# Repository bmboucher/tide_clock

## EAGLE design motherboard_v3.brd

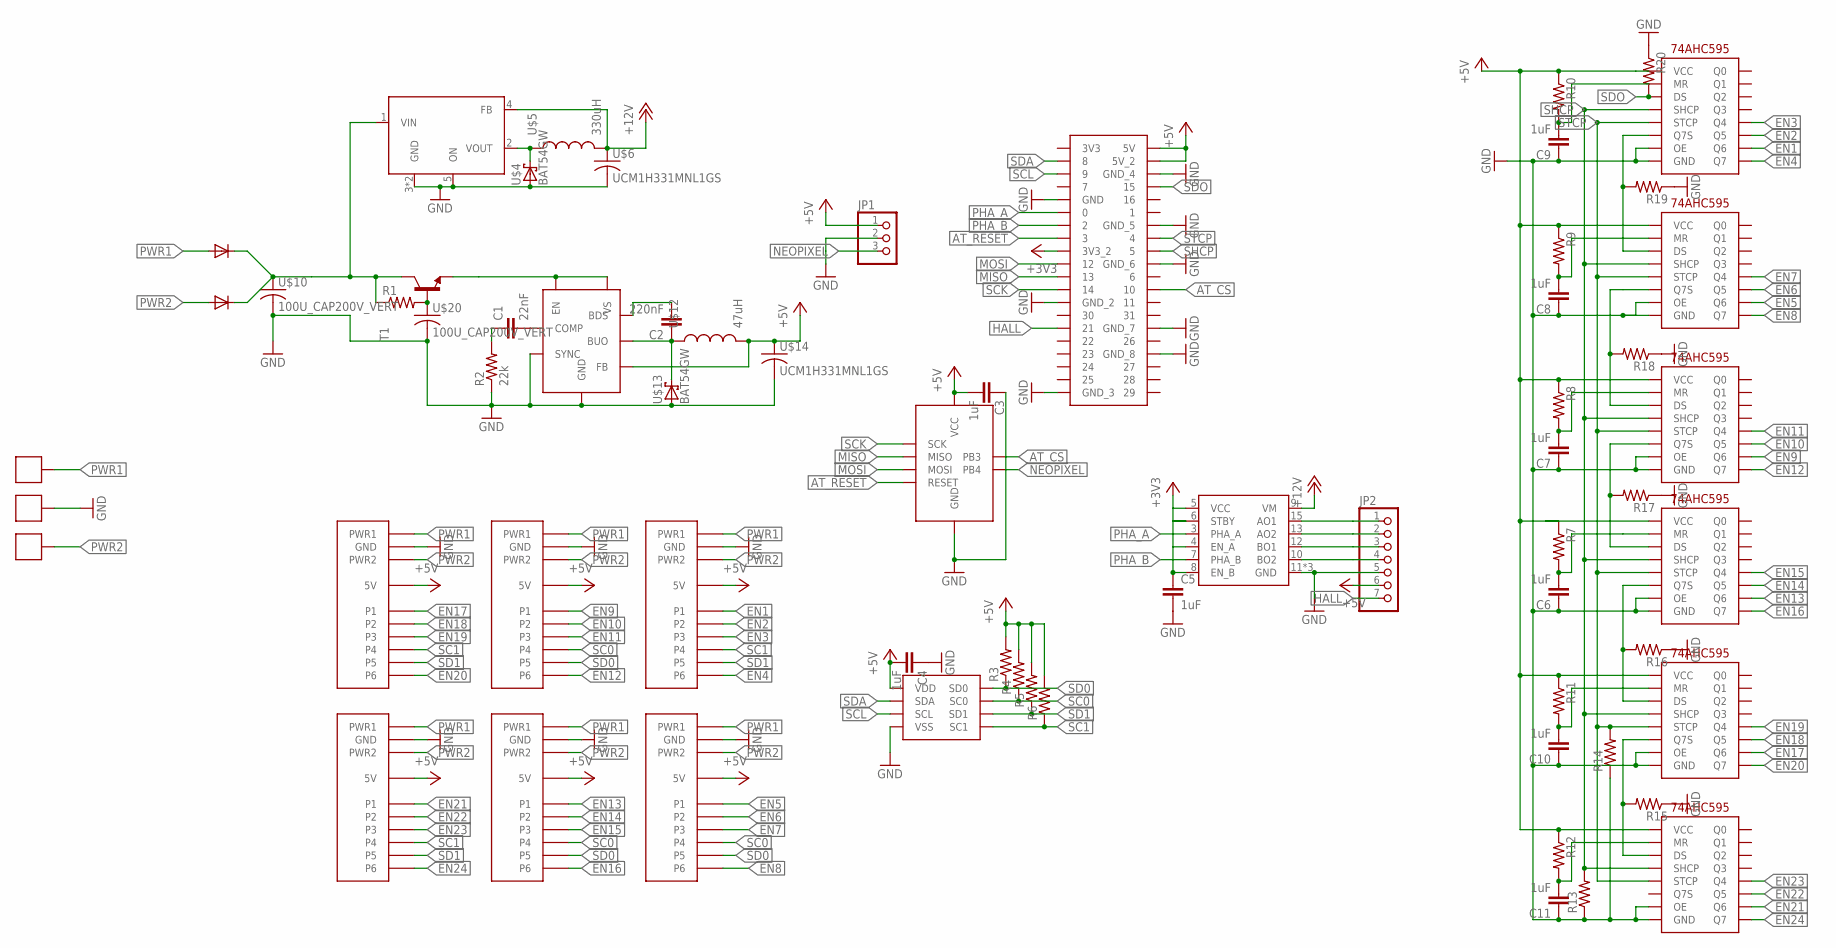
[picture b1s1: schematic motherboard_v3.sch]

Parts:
B1, B2, B3, B4, B5, B6: PCIE_SOCKET
C1: 22nF; C0805
C2: 220nF; C0805
C3, C4, C5, C6, C7, C8, C9, C10, C11: 1uF; C0805
JP1: PINHD-1X3; 1X03
JP2: PINHD-1X7; 1X07
R1: R-US_R1206; R1206
R2: 22k; R1206
R3, R4, R5, R6, R7, R8, R9, R10, R11, R12, R13, R14, R15, R16, R17, R18, R19, R20: R-US_R0805; R0805
T1: -NPN-SOT23-EBC; SOT23-EBC
U1: IFX91041EJV50XUMA1; SOIC127P600X170-8
U$1: RPI_SOCKET; 40PIN_SOCKET
U$2: TC78H620FNG; SSOP16
U$3: TL2575HV-12IKTTR; TO170P1524X483-6
U$4, U$13: BAT54GW; SOD3616X130
U$5: 330uH; SRN8040TA
U$6, U$14: UCM1H331MNL1GS; CAPAE1030X1050
U$7, U$22, U$23, U$24, U$25, U$26: 74HC595_QFN; QFN50P250X350X100-16
U$8, U$9: BAS16GW; SOD3616X130
U$10, U$20: 100U_CAP200V_VERT; VERT_CAP
U$11: ATTINY85; SOIC127P599X175-8
U$12: 47uH; SRN8040TA
U$17, U$18, U$19: 1935310
U$21: PCA9540BDP; TSSOP8

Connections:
+3V3: C5.1, U$1.P17 (3V3_2), U$2.4 (EN_A), U$2.5 (VCC), U$2.6 (STBY), U$2.8 (EN_B)
+5V: B1.5V_1 (5V), B1.5V_2 (5V), B2.5V_1 (5V), B2.5V_2 (5V), B3.5V_1 (5V), B3.5V_2 (5V), B4.5V_1 (5V), B4.5V_2 (5V), B5.5V_1 (5V), B5.5V_2 (5V), B6.5V_1 (5V), B6.5V_2 (5V), C3.2, C4.2, JP1.1, JP2.6, R3.2, R4.2, R5.2, R6.2, R7.1, R8.1, R9.1, R10.1, R11.1, R12.1, U1.4 (FB), U$1.P2 (5V), U$1.P4 (5V_2), U$7.P16 (VCC), U$11.8 (VCC), U$12.P$2 (2), U$14.1, U$21.3 (VDD), U$22.P16 (VCC), U$23.P16 (VCC), U$24.P16 (VCC), U$25.P16 (VCC), U$26.P16 (VCC)
+12V: U$2.9 (VM), U$3.4 (FB), U$5.P$2 (2), U$6.1
AT_CS: U$1.P24 (10), U$11.2 (PB3)
AT_RESET: U$1.P15 (3), U$11.1 (RESET)
EN1: B1.P1, U$7.P6 (Q6)
EN2: B1.P2, U$7.P5 (Q5)
EN3: B1.P3, U$7.P4 (Q4)
EN4: B1.P6, U$7.P7 (Q7)
EN5: B2.P1, U$22.P6 (Q6)
EN6: B2.P2, U$22.P5 (Q5)
EN7: B2.P3, U$22.P4 (Q4)
EN8: B2.P6, U$22.P7 (Q7)
EN9: B3.P1, U$23.P6 (Q6)
EN10: B3.P2, U$23.P5 (Q5)
EN11: B3.P3, U$23.P4 (Q4)
EN12: B3.P6, U$23.P7 (Q7)
EN13: B4.P1, U$24.P6 (Q6)
EN14: B4.P2, U$24.P5 (Q5)
EN15: B4.P3, U$24.P4 (Q4)
EN16: B4.P6, U$24.P7 (Q7)
EN17: B5.P1, U$25.P6 (Q6)
EN18: B5.P2, U$25.P5 (Q5)
EN19: B5.P3, U$25.P4 (Q4)
EN20: B5.P6, U$25.P7 (Q7)
EN21: B6.P1, U$26.P6 (Q6)
EN22: B6.P2, U$26.P5 (Q5)
EN23: B6.P3, U$26.P4 (Q4)
EN24: B6.P6, U$26.P7 (Q7)
GND: B1.GND1 (GND), B1.GND2 (GND), B2.GND1 (GND), B2.GND2 (GND), B3.GND1 (GND), B3.GND2 (GND), B4.GND1 (GND), B4.GND2 (GND), B5.GND1 (GND), B5.GND2 (GND), B6.GND1 (GND), B6.GND2 (GND), C3.1, C4.1, C5.2, C6.1, C7.1, C8.1, C9.1, C10.1, C11.1, JP1.2, JP2.5, R2.1, R13.1, R14.1, R15.1, R16.1, R17.1, R18.1, R19.1, R20.1, U1.1 (SYNC), U1.2 (GND), U1.PAD (GND), U$1.P6 (GND_4), U$1.P9 (GND), U$1.P14 (GND_5), U$1.P20 (GND_6), U$1.P25 (GND_2), U$1.P30 (GND_7), U$1.P34 (GND_8), U$1.P39 (GND_3), U$2.11 (GND), U$2.14 (GND), U$2.16 (GND), U$3.3 (GND), U$3.5 (ON), U$3.6 (GND), U$4.2 (A), U$6.2, U$7.P8 (GND), U$7.P13 (OE), U$7.P$1 (GND), U$10.P$4 (2), U$11.4 (GND), U$13.2 (A), U$14.2, U$18.P$1, U$18.P$2, U$20.P$4 (2), U$21.6 (VSS), U$22.P8 (GND), U$22.P13 (OE), U$22.P$1 (GND), U$23.P8 (GND), U$23.P13 (OE), U$23.P$1 (GND), U$24.P8 (GND), U$24.P13 (OE), U$24.P$1 (GND), U$25.P8 (GND), U$25.P13 (OE), U$25.P$1 (GND), U$26.P8 (GND), U$26.P13 (OE), U$26.P$1 (GND)
HALL: JP2.7, U$1.P29 (21)
MISO: U$1.P21 (13), U$11.6 (MISO)
MOSI: U$1.P19 (12), U$11.5 (MOSI)
unnamed: T1.E, U1.7 (EN), U1.8 (VS)
unnamed: R1.2, T1.B, U$20.P$3 (1)
unnamed: R1.1, T1.C, U$3.1 (VIN), U$8.1 (C), U$9.1 (C), U$10.P$3 (1)
unnamed: C1.2, U1.3 (COMP)
unnamed: C1.1, R2.2
unnamed: C2.2, U1.5 (BDS)
unnamed: C2.1, U1.6 (BUO), U$12.P$1 (1), U$13.1 (C)
unnamed: R19.2, U$7.P9 (Q7S), U$22.P14 (DS)
unnamed: JP2.1, U$2.15 (AO1)
unnamed: JP2.2, U$2.13 (AO2)
unnamed: JP2.3, U$2.12 (BO1)
unnamed: JP2.4, U$2.10 (BO2)
unnamed: U$3.2 (VOUT), U$4.1 (C), U$5.P$1 (1)
unnamed: C6.2, R7.2, U$24.P10 (MR)
unnamed: R18.2, U$22.P9 (Q7S), U$23.P14 (DS)
unnamed: R17.2, U$23.P9 (Q7S), U$24.P14 (DS)
unnamed: C7.2, R8.2, U$23.P10 (MR)
unnamed: C8.2, R9.2, U$22.P10 (MR)
unnamed: C9.2, R10.2, U$7.P10 (MR)
unnamed: R16.2, U$24.P9 (Q7S), U$25.P14 (DS)
unnamed: C10.2, R11.2, U$25.P10 (MR)
unnamed: C11.2, R12.2, U$26.P10 (MR)
unnamed: R15.2, U$25.P9 (Q7S), U$26.P14 (DS)
NEOPIXEL: JP1.3, U$11.3 (PB4)
PHA_A: U$1.P11 (0), U$2.3 (PHA_A)
PHA_B: U$1.P13 (2), U$2.7 (PHA_B)
PWR1: B1.PWR1_1 (PWR1), B1.PWR1_2 (PWR1), B2.PWR1_1 (PWR1), B2.PWR1_2 (PWR1), B3.PWR1_1 (PWR1), B3.PWR1_2 (PWR1), B4.PWR1_1 (PWR1), B4.PWR1_2 (PWR1), B5.PWR1_1 (PWR1), B5.PWR1_2 (PWR1), B6.PWR1_1 (PWR1), B6.PWR1_2 (PWR1), U$8.2 (A), U$17.P$1, U$17.P$2
PWR2: B1.PWR2_1 (PWR2), B1.PWR2_2 (PWR2), B2.PWR2_1 (PWR2), B2.PWR2_2 (PWR2), B3.PWR2_1 (PWR2), B3.PWR2_2 (PWR2), B4.PWR2_1 (PWR2), B4.PWR2_2 (PWR2), B5.PWR2_1 (PWR2), B5.PWR2_2 (PWR2), B6.PWR2_1 (PWR2), B6.PWR2_2 (PWR2), U$9.2 (A), U$19.P$1, U$19.P$2
SC0: B2.P4, B3.P4, B4.P4, R4.1, U$21.5 (SC0)
SC1: B1.P4, B5.P4, B6.P4, R6.1, U$21.8 (SC1)
SCK: U$1.P23 (14), U$11.7 (SCK)
SCL: U$1.P5 (9), U$21.1 (SCL)
SD0: B2.P5, B3.P5, B4.P5, R3.1, U$21.4 (SD0)
SD1: B1.P5, B5.P5, B6.P5, R5.1, U$21.7 (SD1)
SDA: U$1.P3 (8), U$21.2 (SDA)
SDO: R20.2, U$1.P8 (15), U$7.P14 (DS)
SHCP: R13.2, U$1.P18 (5), U$7.P11 (SHCP), U$22.P11 (SHCP), U$23.P11 (SHCP), U$24.P11 (SHCP), U$25.P11 (SHCP), U$26.P11 (SHCP)
STCP: R14.2, U$1.P16 (4), U$7.P12 (STCP), U$22.P12 (STCP), U$23.P12 (STCP), U$24.P12 (STCP), U$25.P12 (STCP), U$26.P12 (STCP)

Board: 2 copper layers, 65 parts (27 on the bottom side), 71 nets, no tracks yet.

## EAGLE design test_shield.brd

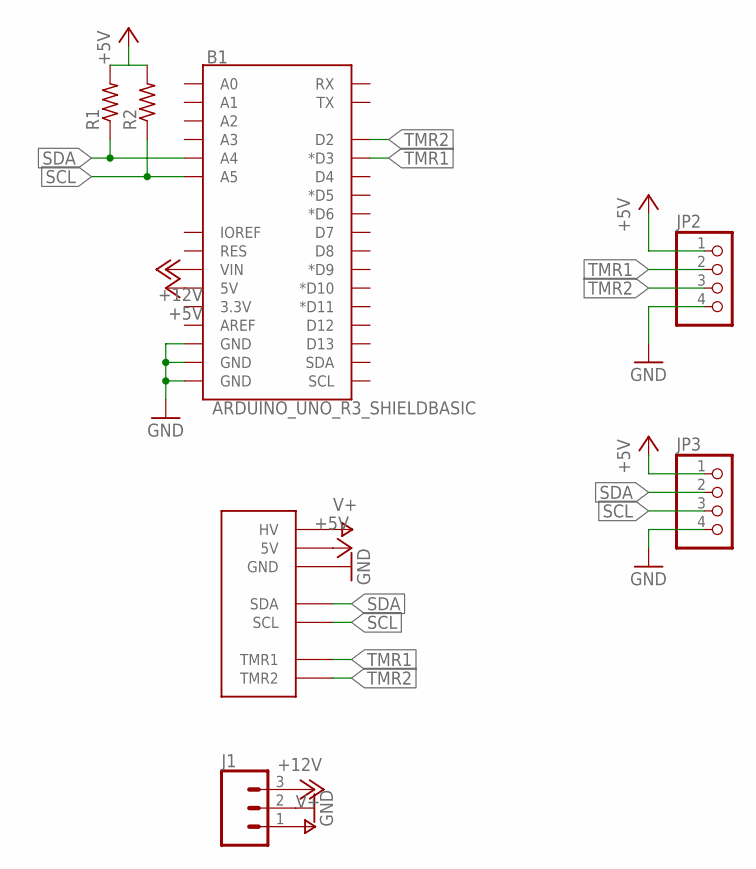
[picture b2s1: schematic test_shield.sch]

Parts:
B1: ARDUINO_UNO_R3_SHIELDBASIC; UNO_R3_SHIELD
J1: CONN_03-SCREW-5MM; SCREWTERMINAL-5MM-3
JP1: PCIE_RA
JP2, JP3: PINHD-1X4; 1X04
R1, R2: R-US_0207/10; 0207/10

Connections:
+5V: B1.5V, JP1.A12 (5V), JP1.A13 (5V), JP1.A14 (5V), JP1.B12 (5V), JP1.B13 (5V), JP1.B14 (5V), JP2.1, JP3.1, R1.2, R2.2
+12V: B1.VIN, J1.3
GND: B1.GND@0 (GND), B1.GND@1 (GND), B1.GND@2 (GND), J1.2, JP1.A1 (GND), JP1.A2 (GND), JP1.A3 (GND), JP1.B1 (GND), JP1.B2 (GND), JP1.B3 (GND), JP2.4, JP3.4
SCL: B1.A5, JP1.A5 (SCL), JP1.B5 (SCL), JP3.3, R2.1
SDA: B1.A4, JP1.A6 (SDA), JP1.B6 (SDA), JP3.2, R1.1
TMR1: B1.D3 (*D3), JP1.A8 (TMR1), JP1.B8 (TMR1), JP2.2
TMR2: B1.D2, JP1.A9 (TMR2), JP1.B9 (TMR2), JP2.3
V+: J1.1, JP1.A16 (HV), JP1.A17 (HV), JP1.A18 (HV), JP1.B16 (HV), JP1.B17 (HV), JP1.B18 (HV)

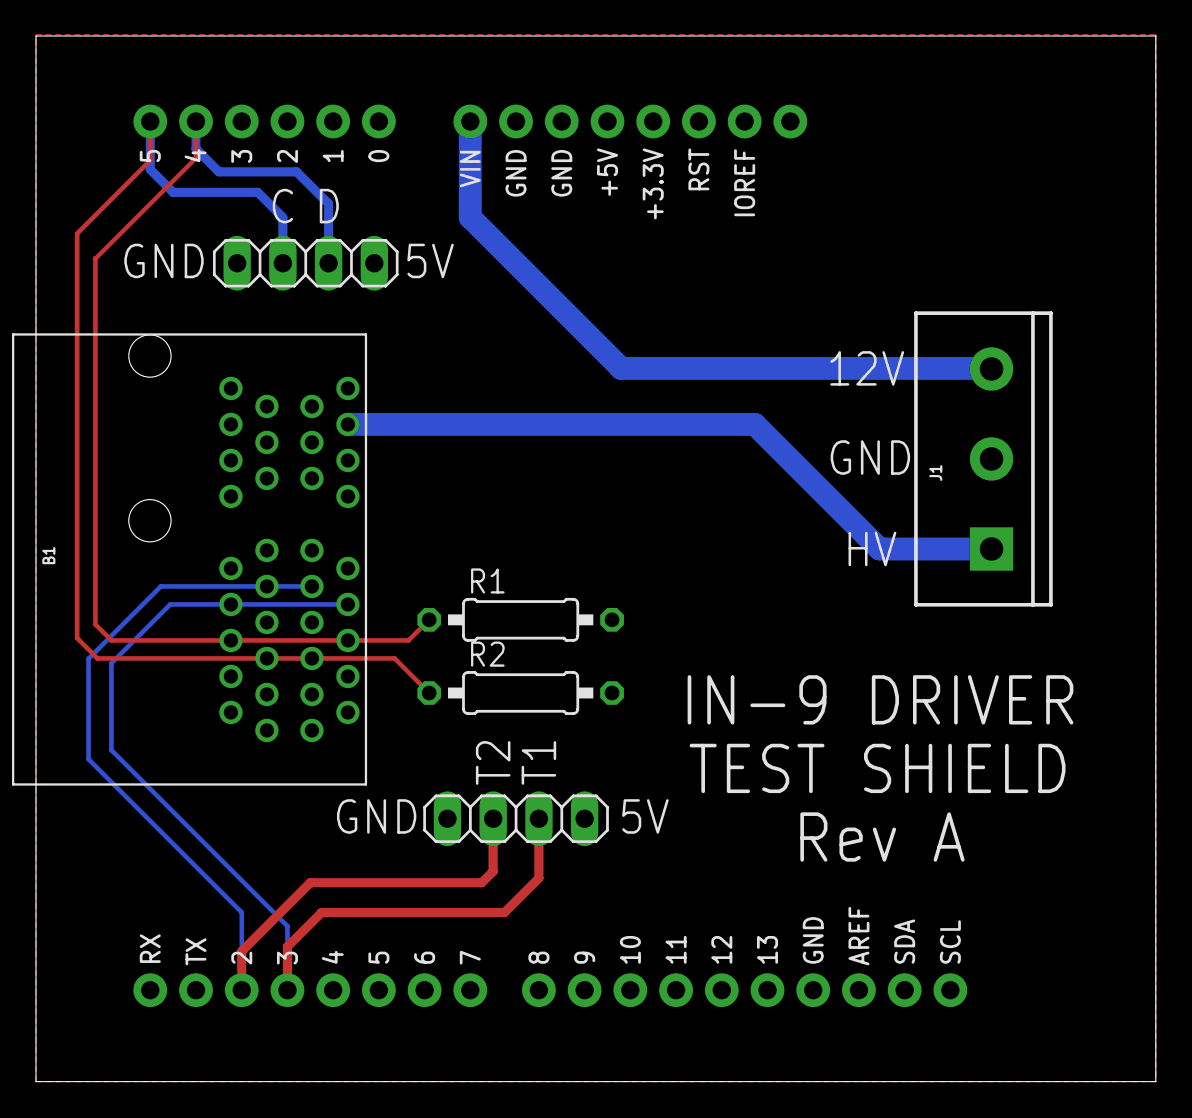
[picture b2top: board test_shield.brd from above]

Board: 2 copper layers, 62.2 x 58.1 mm, 7 parts (0 on the bottom side), 8 nets.

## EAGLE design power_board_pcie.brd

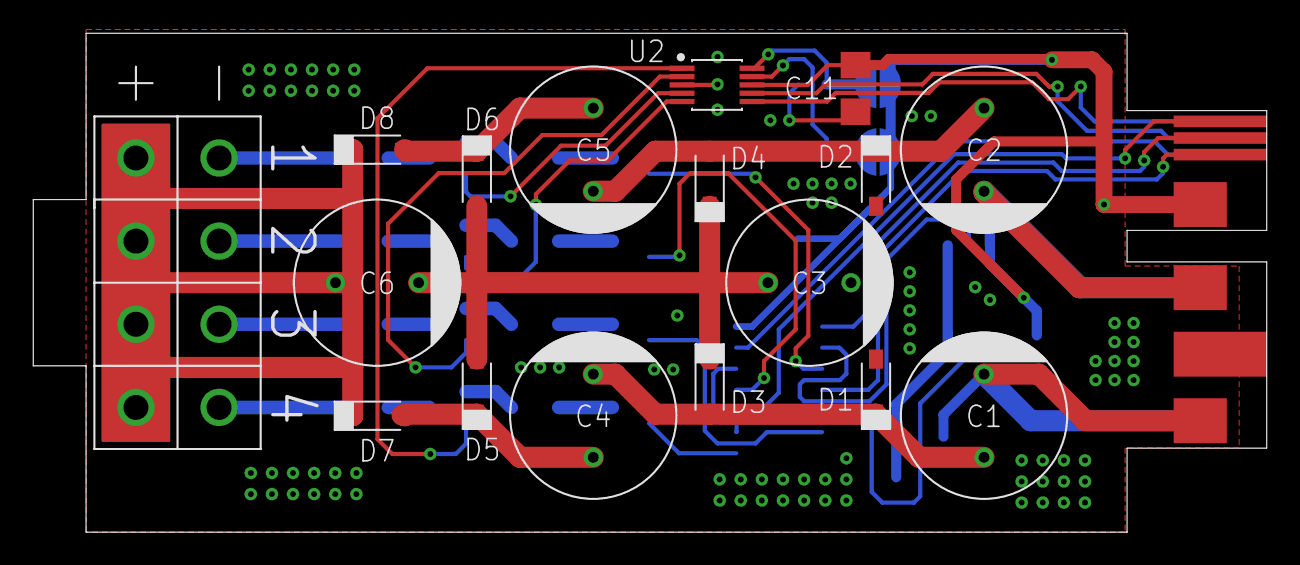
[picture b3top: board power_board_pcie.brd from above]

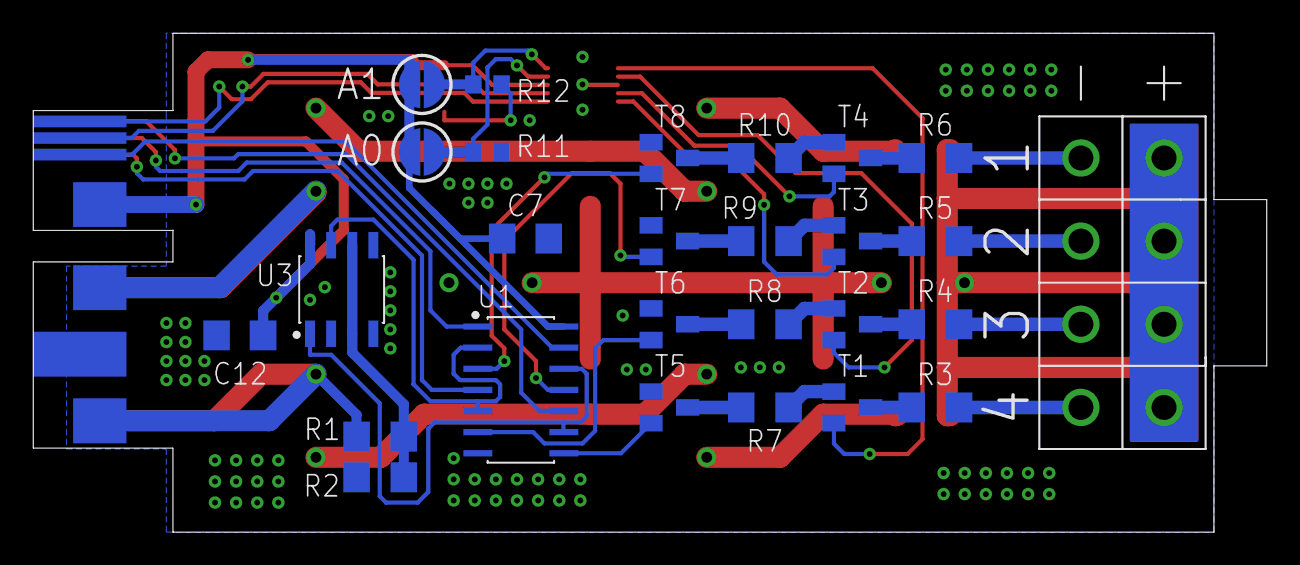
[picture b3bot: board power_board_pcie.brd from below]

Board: 2 copper layers, 74.2 x 30.0 mm, 44 parts (26 on the bottom side), 45 nets.

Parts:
C1, C2, C3, C4, C5, C6: 100U_CAP
C7, C11, C12: C1206
D1, D2, D3, D4, D5, D6, D7, D8: BAS16GW; SOD3616X130
J1: PCIE_EDGE
JP1, JP2: JUMPER-SMT_2_NO_SILK_ROUND; SMT-JUMPER_2_NO_SILK_ROUND
R1, R2, R3, R4, R5, R6, R7, R8, R9, R10: R1206
R11, R12: R0603
T1, T2, T3, T4, T5, T6, T7, T8: SOT23-EBC
U1: 74HCT08D; SOIC127P600X175-14
U2: DAC5574; SOP50P490X110-10
U3: AZ4558CMTR-G1; SOIC127P600X175-8
U$3: POWER_EDGE

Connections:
+5V: C7.1, C11.1, C12.1, J1.PWR3, J1.PWR3_2, JP1.1, JP2.1, U1.14, U2.8, U3.8
EN1: J1.P6, U1.13
EN2: J1.P3, U1.10
EN3: J1.P2, U1.1
EN4: J1.P1, U1.4
GND: C3.C, C7.2, C11.2, C12.2, D1.2, D2.2, J1.P$2, J1.P$5, R2.1, R11.2, R12.2, T5.E, T6.E, T7.E, T8.E, U1.7, U2.3, U3.2, U3.4, U3.5
unnamed: R7.2, T1.E
unnamed: R1.1, R2.2, U3.3, U3.6
unnamed: R3.1, T1.C
unnamed: C3.A, C6.C, D3.1, D4.1, D5.2, D6.2
unnamed: C1.A, C4.C, D1.1, D3.2
unnamed: C2.A, C5.C, D2.1, D4.2
unnamed: C4.A, D5.1, D7.2
unnamed: C5.A, D6.1, D8.2
unnamed: R3.2, U$3.C1
unnamed: R4.2, U$3.C2
unnamed: R5.2, U$3.C3
unnamed: R4.1, T2.C
unnamed: R6.2, U$3.C4
unnamed: R5.1, T3.C
unnamed: R6.1, T4.C
unnamed: R7.1, T5.C
unnamed: T2.B, U2.2
unnamed: T3.B, U2.5
unnamed: T4.B, U2.4
unnamed: T1.B, U2.1
unnamed: R8.2, T2.E
unnamed: R9.2, T3.E
unnamed: R10.2, T4.E
unnamed: R8.1, T6.C
unnamed: R9.1, T7.C
unnamed: R10.1, T8.C
unnamed: JP1.2, R11.1, U2.9
unnamed: JP2.2, R12.1, U2.10
PH_EN1: U1.9, U1.12, U3.1
PH_EN2: U1.2, U1.5, U3.7
PWR1: C1.C, J1.P$1, J1.P$4, R1.2
PWR2: C2.C, J1.P$3, J1.P$6
SCL: J1.P4, U2.6
SDA: J1.P5, U2.7
SW1: T8.B, U1.3
SW2: T6.B, U1.6
SW3: T5.B, U1.8
SW4: T7.B, U1.11
V+: C6.A, D7.1, D8.1, U$3.A1, U$3.A2, U$3.A3, U$3.A4

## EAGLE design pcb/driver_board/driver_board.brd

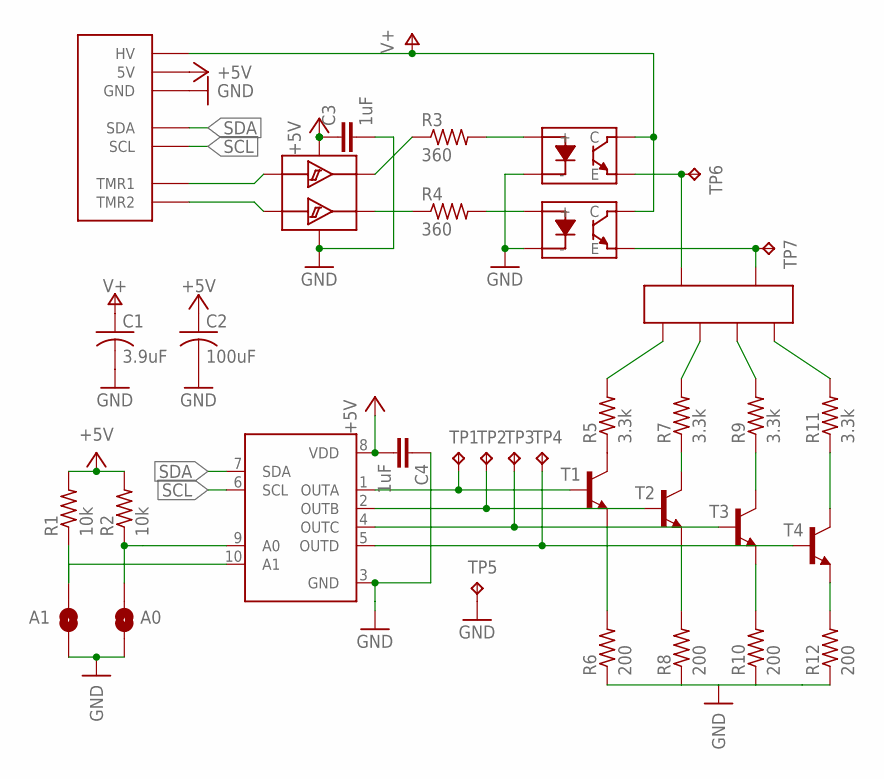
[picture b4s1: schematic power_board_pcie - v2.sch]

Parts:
A0, A1: JUMPER-SMT_2_NO_SILK_ROUND; SMT-JUMPER_2_NO_SILK_ROUND
C1: 3.9uF; CAPAE830X1030
C2: 100uF; CAPAE530X550
C3, C4: 1uF; C1206
J1: PCIE_EDGE
JP3: POWER_EDGE
R1, R2: 10k; R1206
R3, R4: 360; R1206
R5, R7, R9, R11: 3.3k; R2512
R6, R8, R10, R12: 200; R1206
T1, T2, T3, T4: MMBT4401LT1-NPN-SOT23-BEC; SOT23-BEC
TP1, TP2, TP3, TP4, TP5, TP6, TP7: TPB2,54; B2,54
U1: TC7PZ17FU; SOP65P210X100-6
U2: DAC5574; SOP50P490X110-10
U3, U4: LTV-352T; SOP254P675X220-4

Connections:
+5V: C2.1, C3.1, C4.2, J1.5V1 (5V), J1.5V2 (5V), R1.2, R2.2, U1.5 (VCC), U2.8 (VDD)
GND: A0.1, A1.1, C1.2, C2.2, C3.2, C4.1, J1.GND1 (GND), J1.GND2 (GND), R6.1, R8.1, R10.1, R12.1, TP5.TP, U1.2 (GND), U2.3 (GND), U3.2 (-), U4.2 (-)
unnamed: R3.2, U3.1 (+)
unnamed: R4.2, U4.1 (+)
unnamed: R3.1, U1.6 (1Y)
unnamed: R4.1, U1.4 (2Y)
unnamed: JP3.A3 (A2), JP3.A4 (A2), TP7.TP, U4.3 (E)
unnamed: JP3.A1, JP3.A2 (A1), TP6.TP, U3.3 (E)
unnamed: JP3.C1, R5.2
unnamed: JP3.C2, R7.2
unnamed: JP3.C3, R9.2
unnamed: JP3.C4, R11.2
unnamed: R5.1, T1.C
unnamed: R7.1, T2.C
unnamed: R9.1, T3.C
unnamed: R11.1, T4.C
unnamed: R6.2, T1.E
unnamed: R8.2, T2.E
unnamed: R10.2, T3.E
unnamed: R12.2, T4.E
unnamed: T1.B, TP1.TP, U2.1 (OUTA)
unnamed: T2.B, TP2.TP, U2.2 (OUTB)
unnamed: T3.B, TP3.TP, U2.4 (OUTC)
unnamed: T4.B, TP4.TP, U2.5 (OUTD)
unnamed: A0.2, R2.1, U2.9 (A0)
unnamed: A1.2, R1.1, U2.10 (A1)
SCL: J1.SCL1 (SCL), J1.SCL2 (SCL), U2.6 (SCL)
SDA: J1.SDA1 (SDA), J1.SDA2 (SDA), U2.7 (SDA)
TMR1: J1.TMR1_1 (TMR1), J1.TMR1_2 (TMR1), U1.1 (1A)
TMR2: J1.TMR2_1 (TMR2), J1.TMR2_2 (TMR2), U1.3 (2A)
V+: C1.1, J1.HV1 (HV), J1.HV2 (HV), U3.4 (C), U4.4 (C)

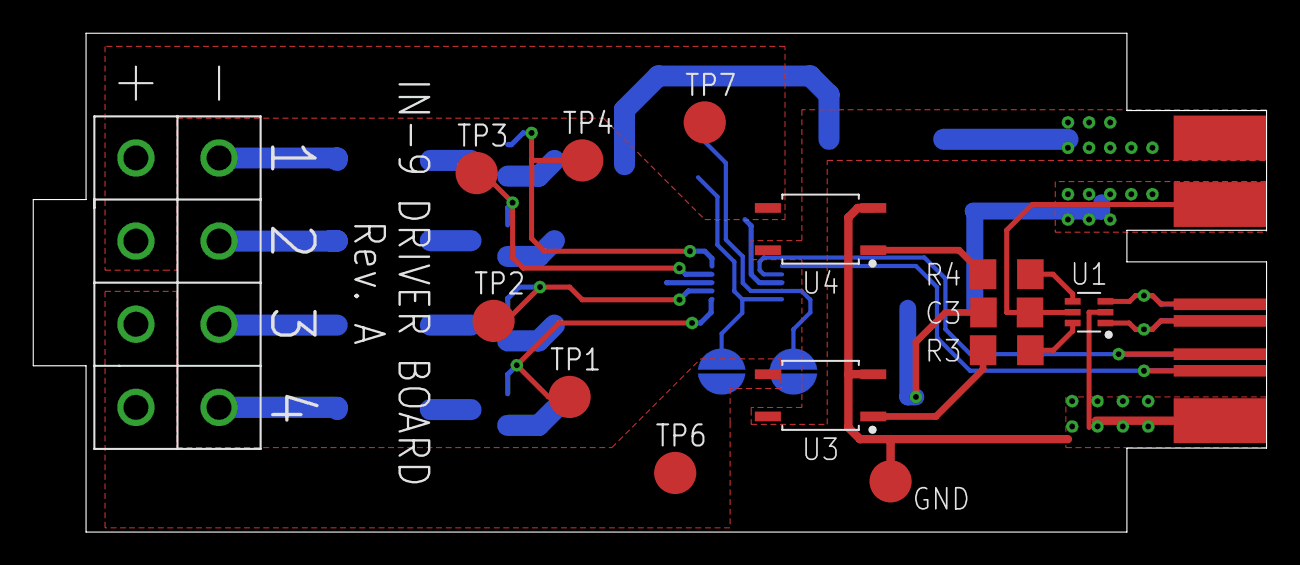
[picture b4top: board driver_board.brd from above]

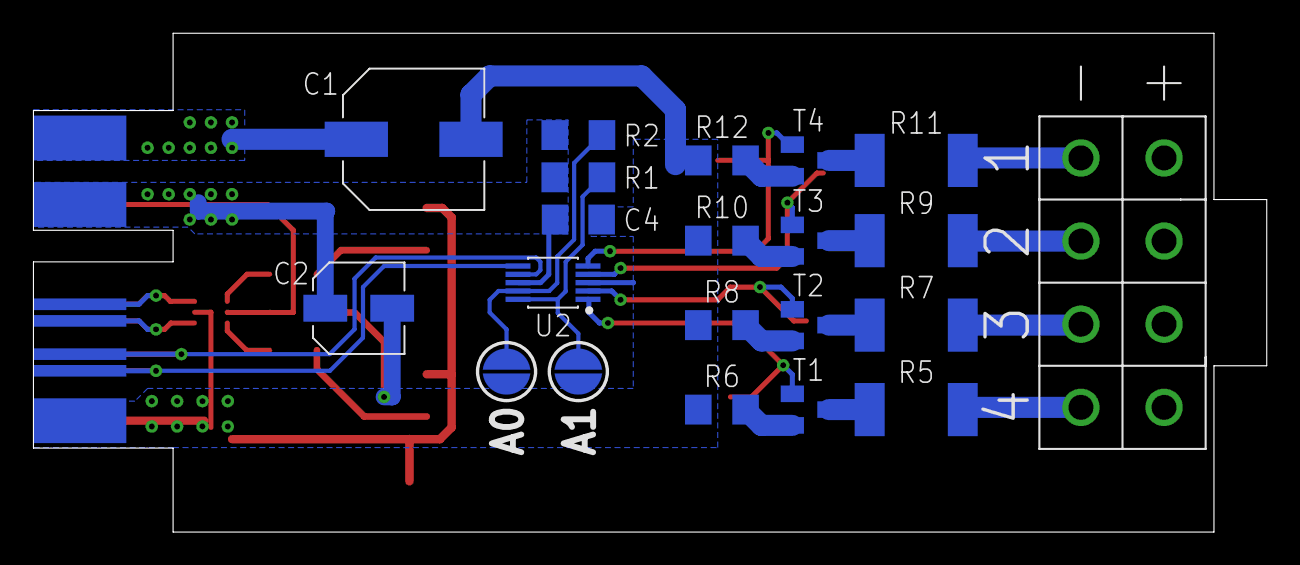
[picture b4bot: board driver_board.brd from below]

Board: 2 copper layers, 74.2 x 30.0 mm, 35 parts (20 on the bottom side), 31 nets.

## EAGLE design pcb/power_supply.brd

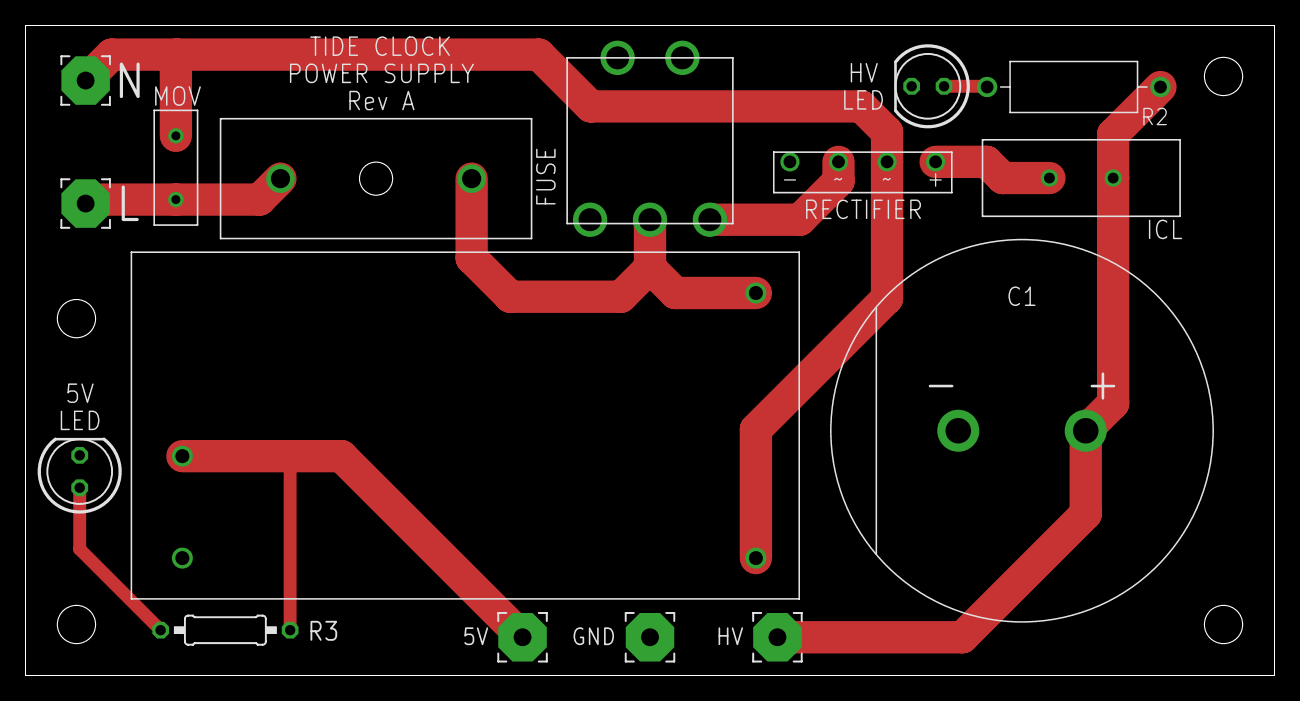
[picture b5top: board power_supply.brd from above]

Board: 2 copper layers, 98.0 x 51.0 mm, 16 parts (0 on the bottom side), 10 nets.

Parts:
5V: WIREPAD3,81/1,4; 3,81/1,4
C1: ESMQ201VSN122MR30S; CAPPRD1000W200D3000H3000B
D1: UG6KB100TB
F1: 20MM_FUSEHOLDER
GND: WIREPAD3,81/1,4; 3,81/1,4
HV: WIREPAD3,81/1,4; 3,81/1,4
L: WIREPAD3,81/1,4; 3,81/1,4
LED1, LED2: LED5MM
M1: IRM-15-5
N: WIREPAD3,81/1,4; 3,81/1,4
R1: MF72-030D13
R2: RR02J20KTB; RESAD1360W80L900D350B
R3: 0207/10
SW1: M2013S2A2W30
V1: MOV-07D201K

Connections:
GND: C1.-, D1.-, GND.1, LED1.K, LED2.K, M1.-
unnamed: D1.+, R1.P$1
unnamed: C1.+, HV.1, R1.P$2, R2.2
unnamed: F1.P$2, M1.L, SW1.2
unnamed: F1.P$1, L.1, V1.P$2
unnamed: D1.AC1, SW1.3
unnamed: 5V.1, M1.+, R3.2
unnamed: LED1.A, R2.1
unnamed: D1.AC2, M1.N, N.1, V1.P$1
unnamed: LED2.A, R3.1

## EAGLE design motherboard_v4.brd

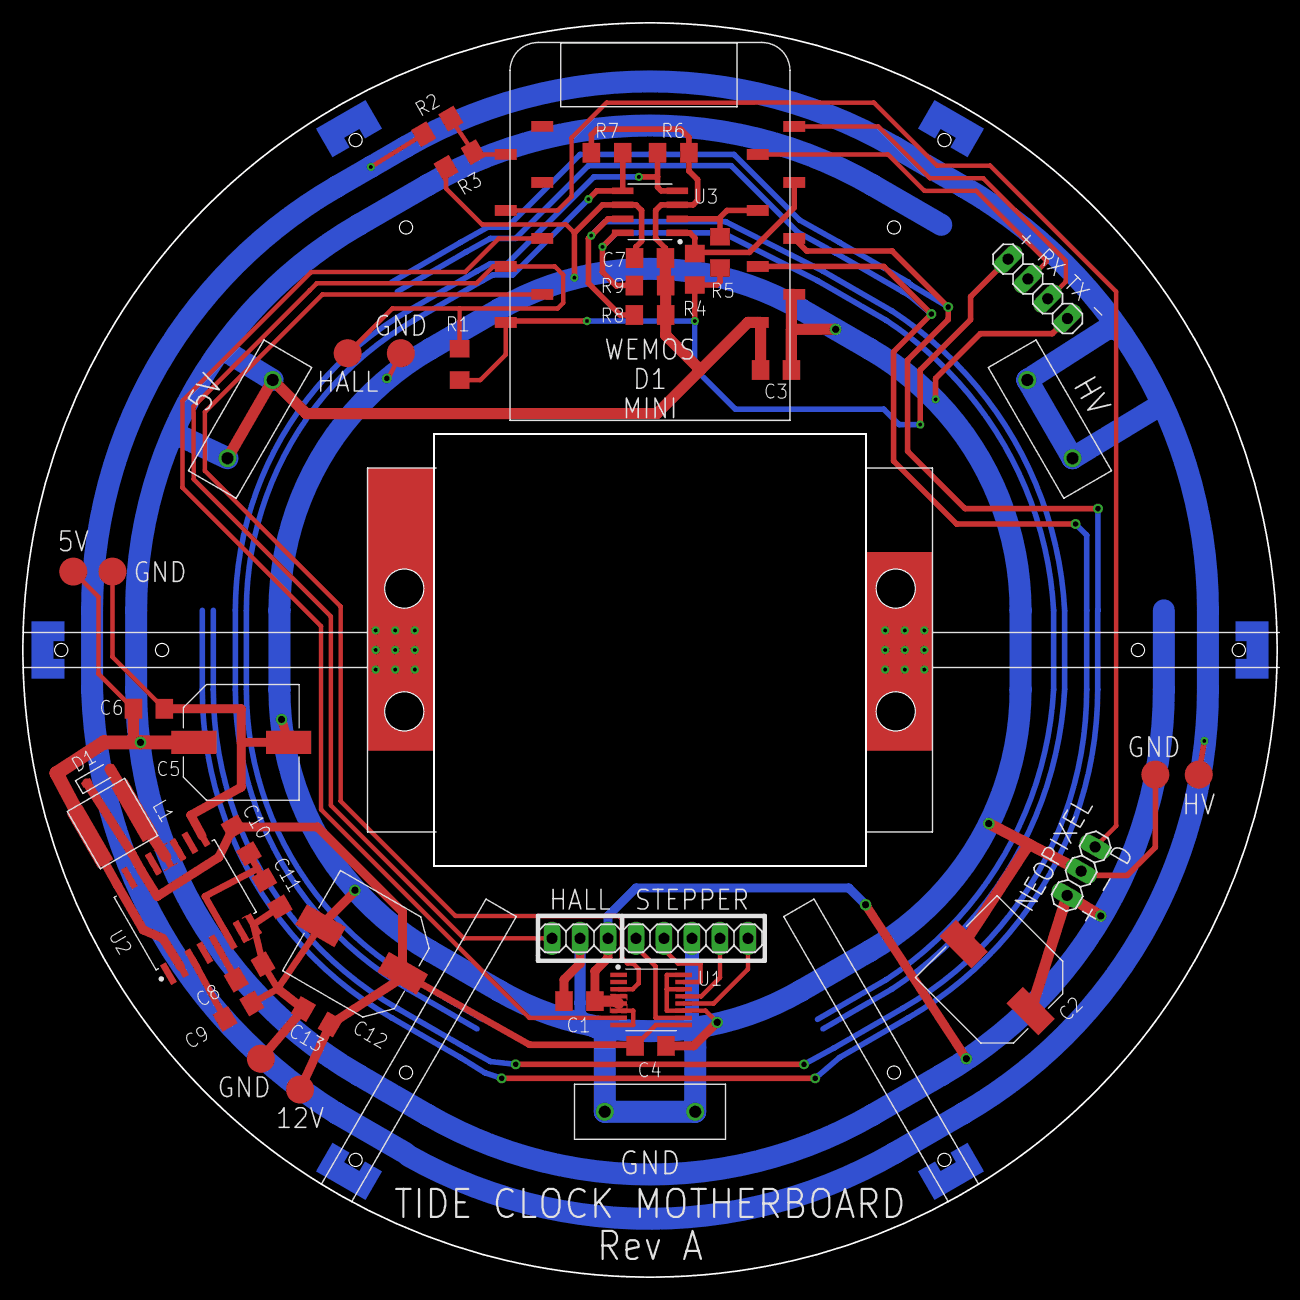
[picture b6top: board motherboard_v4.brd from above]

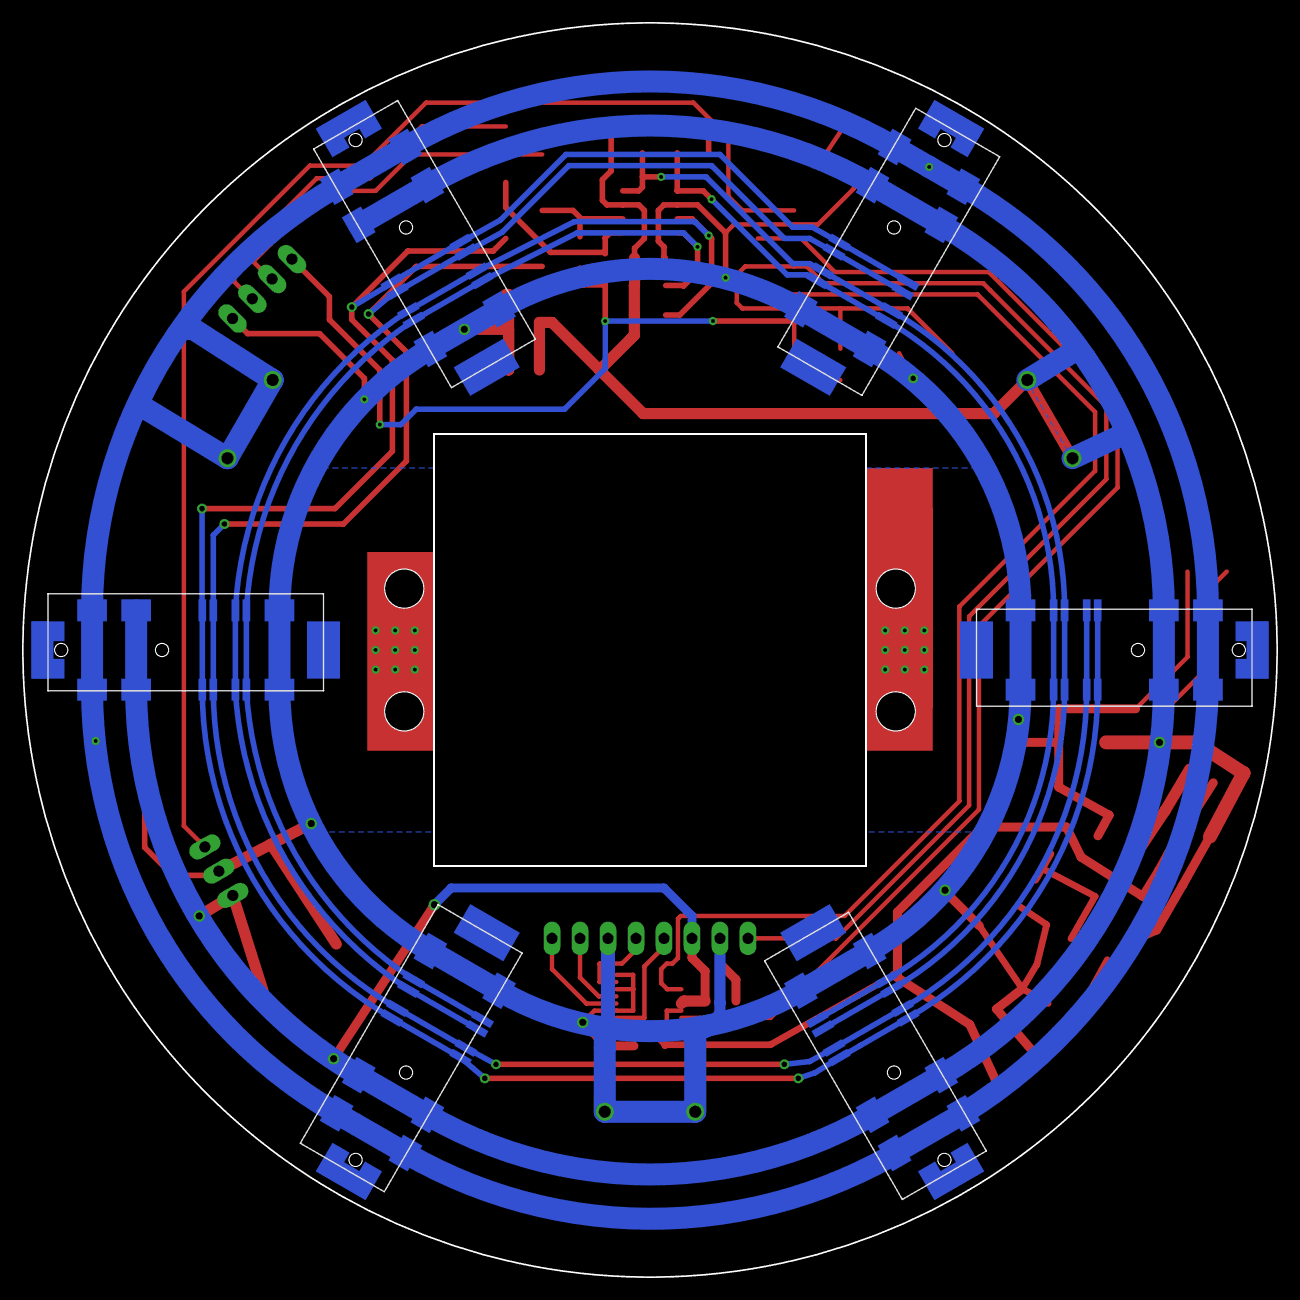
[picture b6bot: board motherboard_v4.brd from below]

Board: 2 copper layers, 113.8 x 113.8 mm, 48 parts (6 on the bottom side), 28 nets.

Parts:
C1, C4, C6, C7, C13: 1uF; C1206
C2, C5, C12: UCM1H331MNL1GS; CAPAE1030X1050
C3: 1 uF; C1206
C8: 0.1uF; C1206
C9: 0.01uF; C1206
C10: 0.15uF; C1206
C11: 2200pF; C1206
D1: NSR0530H; SOD2512X100
J1, J2, J3: PHOENIX_1731468
JP1: 1X04
JP2, JP3, JP5, JP7, JP8, JP9: PCIE_SOCKET
JP4: 1X03
JP6: 1X08
L1: NR6028
R1, R4, R5: 4.7k; R1206
R2: 200k; R1206
R3: 2.8k; R1206
R6, R7, R8, R9: R1206
TP1, TP2, TP3, TP4, TP5, TP6, TP7, TP8: TPB2,54; B2,54
U1: TC78H620FNG; SSOP16
U2: MAX732; SOIC127P1032X265-16
U3: PCA9540BDPSOIC8; SOIC127P599X175-8
WEMOS1: WEMOS-D1-MINI-SMD

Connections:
+3V3: JP1.1, R1.1, R4.2, R5.2, WEMOS1.3V3
+5V: C1.2, C2.1, C3.2, C5.1, C6.1, C7.2, J2.P$1, J2.P$2, JP2.5V1, JP2.5V2, JP3.5V1, JP3.5V2, JP4.1, JP5.5V1, JP5.5V2, JP6.3, JP7.5V1, JP7.5V2, JP8.5V1, JP8.5V2, JP9.5V1, JP9.5V2, L1.1, R6.2, R7.2, R8.2, R9.2, TP6.TP, U1.4, U1.5, U1.6, U1.8, U2.2, U2.16, U3.3, WEMOS1.5V
+12V: C4.1, C10.2, C12.1, C13.2, D1.1, TP2.TP, U1.9, U2.14
AO1: JP6.5, U1.15
AO2: JP6.7, U1.13
BO1: JP6.8, U1.12
BO2: JP6.4, U1.10
GND: C1.1, C2.2, C3.1, C4.2, C5.2, C6.2, C7.1, C8.1, C9.1, C11.1, C12.2, C13.1, J3.P$1, J3.P$2, JP1.4, JP2.GND1, JP2.GND2, JP3.GND1, JP3.GND2, JP4.2, JP5.GND1, JP5.GND2, JP6.2, JP6.6, JP7.GND1, JP7.GND2, JP8.GND1, JP8.GND2, JP9.GND1, JP9.GND2, R3.2, TP1.TP, TP4.TP, TP5.TP, TP7.TP, U1.11, U1.14, U1.16, U2.7, U2.8, U2.9, U3.6, WEMOS1.GND
HALL: JP6.1, R1.2, TP3.TP, WEMOS1.D7
unnamed: D1.2, L1.2, U2.11, U2.12, U2.13
unnamed: C10.1, C11.2, U2.6
unnamed: C9.2, U2.3
unnamed: C8.2, U2.5
unnamed: R2.2, R3.1, WEMOS1.A0
NEOPIXEL: JP4.3, WEMOS1.D5
PHA_A: U1.3, WEMOS1.D8
PHA_B: U1.7, WEMOS1.D6
RX: JP1.2, WEMOS1.RX
SC0: JP2.SCL1, JP2.SCL2, JP3.SCL1, JP3.SCL2, JP5.SCL1, JP5.SCL2, R7.1, U3.5
SC1: JP7.SCL1, JP7.SCL2, JP8.SCL1, JP8.SCL2, JP9.SCL1, JP9.SCL2, R9.1, U3.8
SCL: R4.1, U3.1, WEMOS1.D1
SD0: JP2.SDA1, JP2.SDA2, JP3.SDA1, JP3.SDA2, JP5.SDA1, JP5.SDA2, R6.1, U3.4
SD1: JP7.SDA1, JP7.SDA2, JP8.SDA1, JP8.SDA2, JP9.SDA1, JP9.SDA2, R8.1, U3.7
SDA: R5.1, U3.2, WEMOS1.D2
TMR1: JP2.TMR1_1, JP2.TMR1_2, JP3.TMR1_1, JP3.TMR1_2, JP5.TMR1_1, JP5.TMR1_2, JP7.TMR1_1, JP7.TMR1_2, JP8.TMR1_1, JP8.TMR1_2, JP9.TMR1_1, JP9.TMR1_2, WEMOS1.D4
TMR2: JP2.TMR2_1, JP2.TMR2_2, JP3.TMR2_1, JP3.TMR2_2, JP5.TMR2_1, JP5.TMR2_2, JP7.TMR2_1, JP7.TMR2_2, JP8.TMR2_1, JP8.TMR2_2, JP9.TMR2_1, JP9.TMR2_2, WEMOS1.D3
TX: JP1.3, WEMOS1.TX
V+: J1.P$1, J1.P$2, JP2.HV1, JP2.HV2, JP3.HV1, JP3.HV2, JP5.HV1, JP5.HV2, JP7.HV1, JP7.HV2, JP8.HV1, JP8.HV2, JP9.HV1, JP9.HV2, R2.1, TP8.TP

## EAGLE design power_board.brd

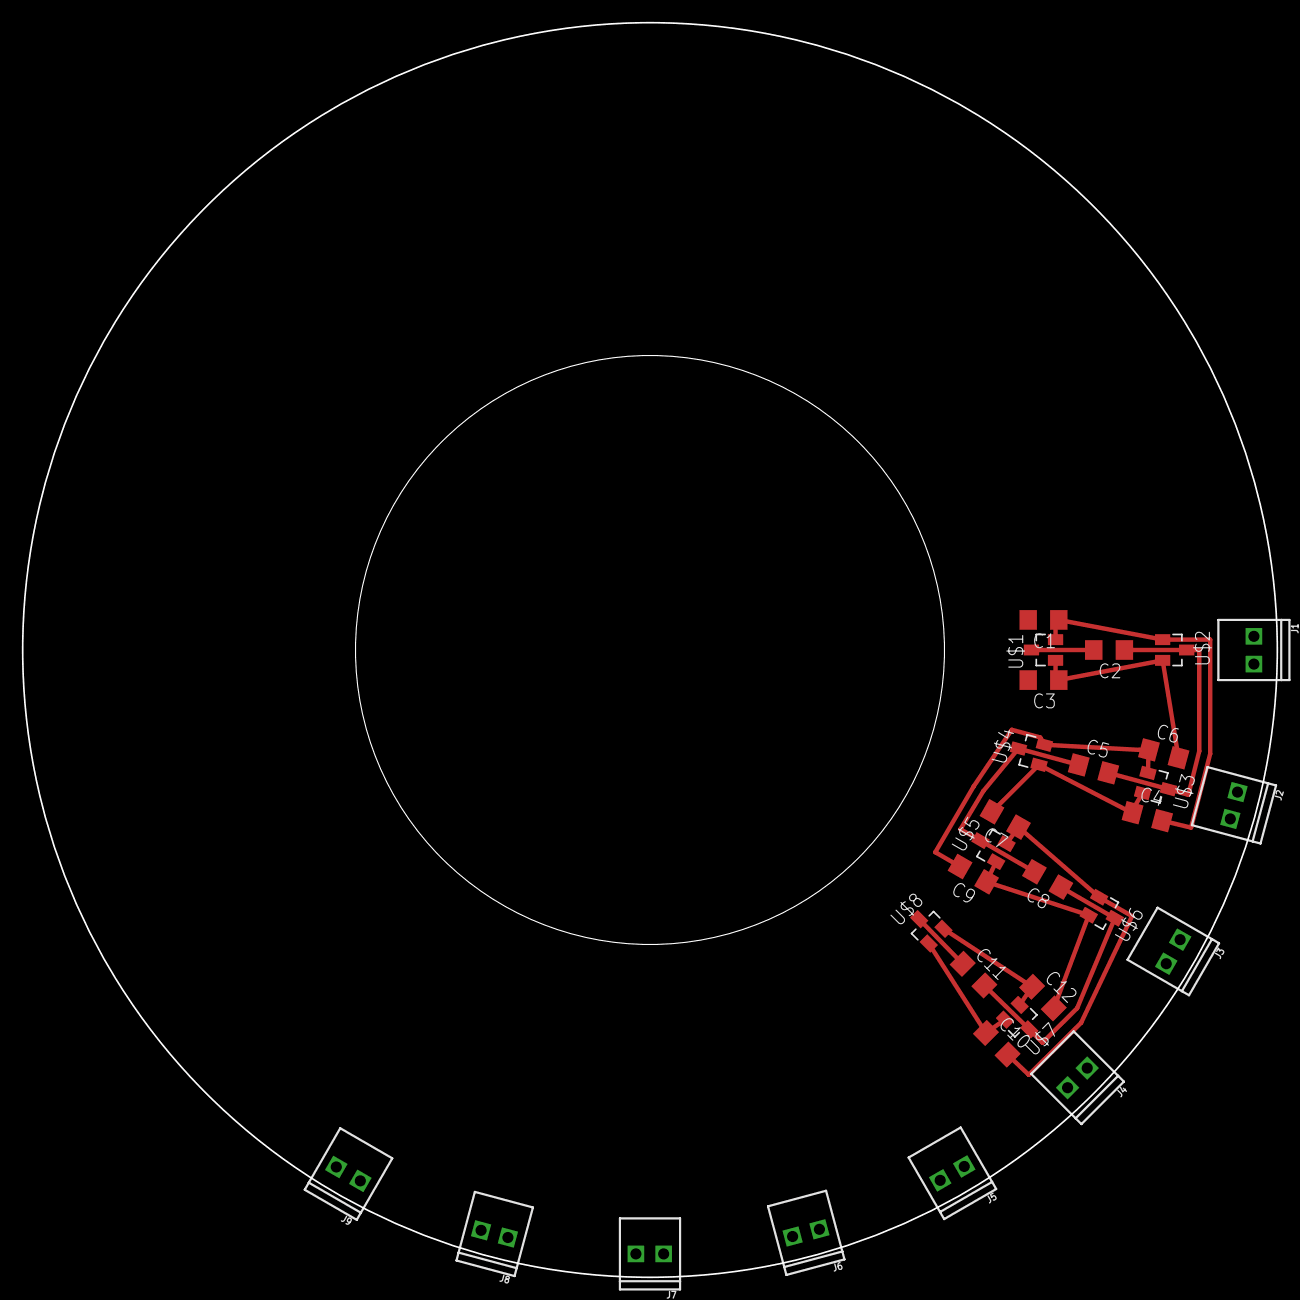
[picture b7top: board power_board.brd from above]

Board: 2 copper layers, 114.8 x 114.8 mm, 29 parts (0 on the bottom side), 13 nets.

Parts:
C1, C2, C3, C4, C5, C6, C7, C8, C9, C10, C11, C12: C1206
J1, J2, J3, J4, J5, J6, J7, J8, J9: 1X02_2.54_SCREWTERM
U$1, U$3, U$5, U$7: BAT54AT; SOT23
U$2, U$4, U$6, U$8: BAT54CT; SOT23

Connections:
GND: C2.2, U$1.3
GND1: C2.1, C5.2, U$2.3, U$3.3
GND2: C5.1, C8.2, U$4.3, U$5.3
GND3: C8.1, C11.2, U$6.3, U$7.3
unnamed: C7.1, C10.2, U$5.2, U$6.1
unnamed: C9.1, C12.2, U$5.1, U$6.2
unnamed: C10.1, U$7.2, U$8.1
unnamed: C12.1, U$7.1, U$8.2
unnamed: C11.1, U$8.3
V+1: C1.1, C4.2, U$1.2, U$2.1
V+2: C4.1, C7.2, U$3.2, U$4.1
V-1: C3.1, C6.2, U$1.1, U$2.2
V-2: C6.1, C9.2, U$3.1, U$4.2

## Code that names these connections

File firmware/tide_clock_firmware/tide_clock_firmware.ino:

#include "tide_clock_firmware.h"

void setup() {
  pinMode(MAIN_BUS, INPUT);
  pinMode(TMR1, OUTPUT);
  pinMode(TMR2, OUTPUT);
  pinMode(PHA_A, OUTPUT);
  pinMode(PHA_B, OUTPUT);
  pinMode(NEOPIXEL, OUTPUT);
  pinMode(HALL, INPUT);
  pinMode(LED_BUILTIN, OUTPUT);
  digitalWrite(LED_BUILTIN, HIGH);

  Serial.begin(115200);

  connect_to_wifi();
  update_tides();
  setup_eeprom();
  init_dacs();
  init_display();
  
  init_position();  
  start_server();

  // Turn on status LED
  digitalWrite(LED_BUILTIN, LOW);
  init_loop_timer();
}

void loop() {
  update_tides();
  check_main_bus_voltage();
  update_time_position();
  display_loop();
  server_loop();
  mark_loop_timer();
}

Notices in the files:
parts and their libraries:
SparkFun-Jumpers: Licensing: Creative Commons ShareAlike 4.0 International - https://creativecommons.org/licenses/by-sa/4.0
